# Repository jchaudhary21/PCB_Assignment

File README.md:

# PCB Design Based on F4BY board

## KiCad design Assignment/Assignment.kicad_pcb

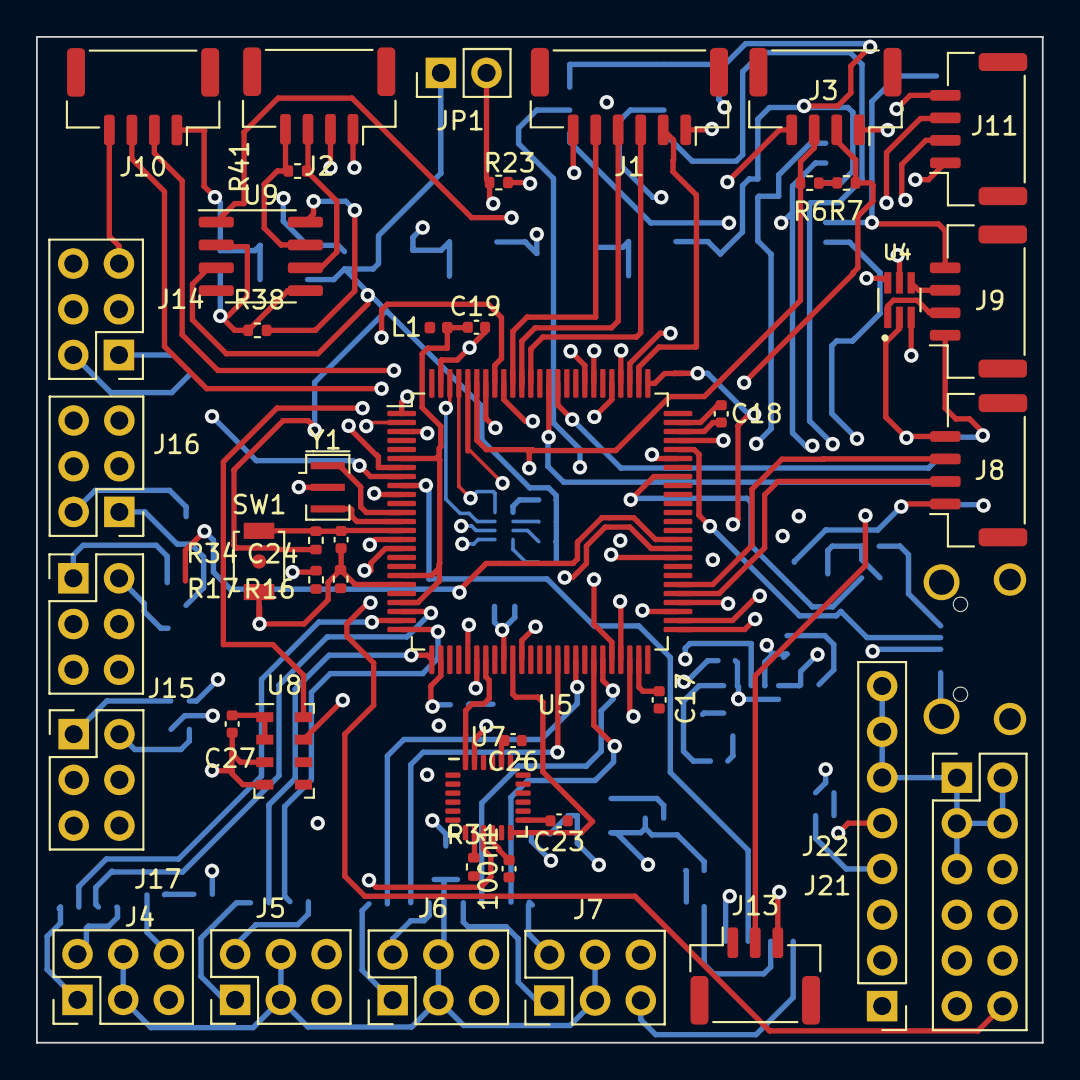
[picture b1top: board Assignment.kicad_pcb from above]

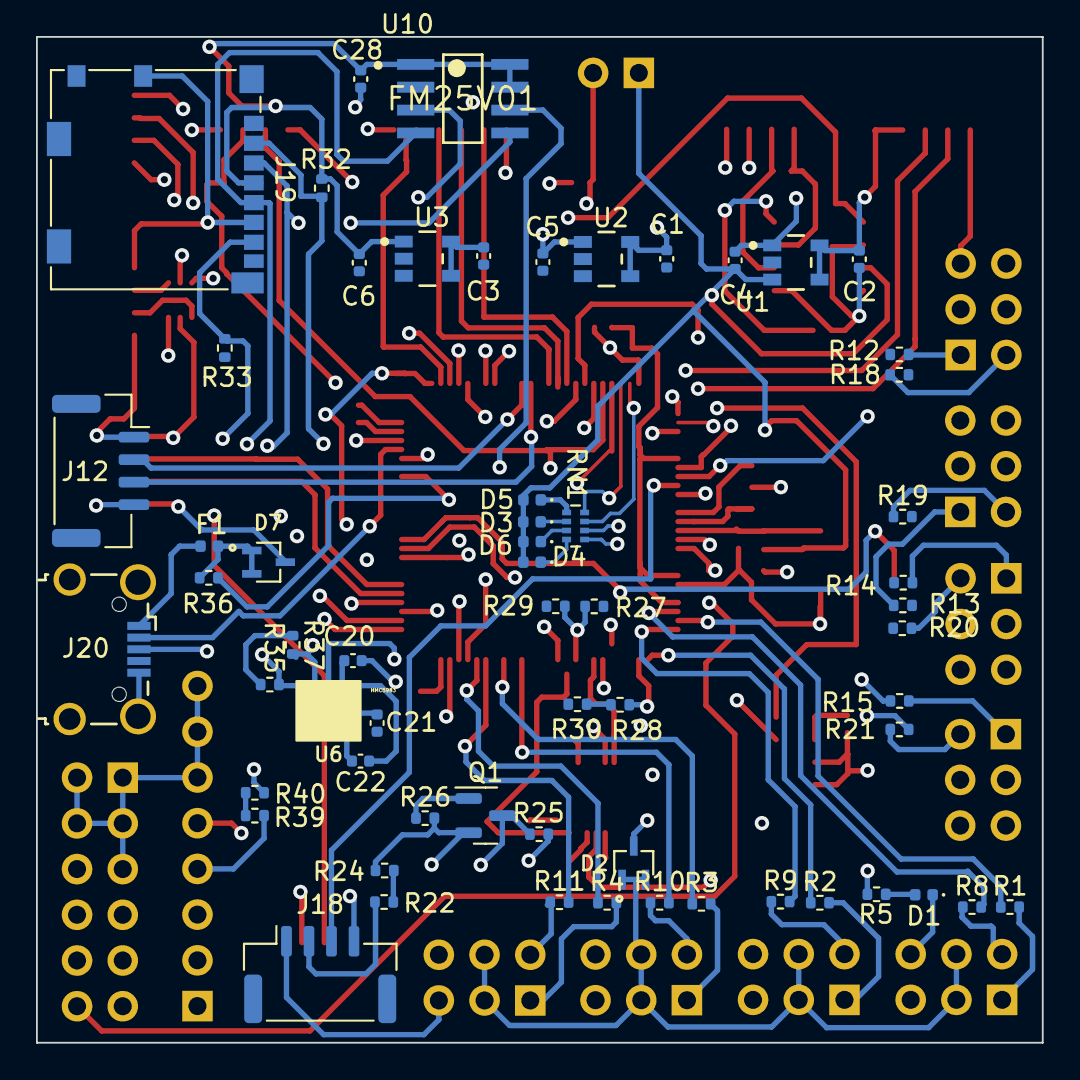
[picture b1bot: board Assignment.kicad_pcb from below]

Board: 4 copper layers, 55.9 x 55.9 mm, 105 parts (61 on the bottom side), 116 nets.

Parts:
100n1: C; C_0402_1005Metric
C1, C2, C3: 1uF; C_0402_1005Metric
C4, C5, C6: 2.2uF; C_0402_1005Metric
C17, C18, C20, C21, C22, C27: C; C_0402_1005Metric
C19, C24: C_Small; C_0402_1005Metric
C23, C26, C28: 100n; C_0402_1005Metric
D1, D3, D4, D5, D6: LED; LED_0402_1005Metric
D2, D7: Dual_Diode; SOT65P205X100-3N
F1: 500mA; Fuse_0402_1005Metric
J1: Conn_01x06_Male; JST_GH_SM06B-GHS-TB_1x06-1MP_P1.25mm_Horizontal
J2, J3, J8, J9, J10, J11, J12, J18: Conn_01x04_Male; JST_GH_SM04B-GHS-TB_1x04-1MP_P1.25mm_Horizontal
J4, J5, J6, J7, J14, J15, J16, J17: Conn_02x03_Odd_Even; PinHeader_2x03_P2.54mm_Vertical
J13: Conn_01x03_Male; JST_GH_SM03B-GHS-TB_1x03-1MP_P1.25mm_Horizontal
J19: Micro_SD_Card; microSD_HC_Molex_104031-0811
J20: USB_B_Micro; USB_Micro-B_Wuerth_629105150521_CircularHoles
J21: Conn_02x06_Counter_Clockwise; PinHeader_2x06_P2.54mm_Vertical
J22: Conn_01x08_Male; PinHeader_1x08_P2.54mm_Vertical
JP1: Solder Jumper; PinHeader_1x02_P2.54mm_Vertical
L1: INDUCTOR (L_1); L_0402_1005Metric
Q1: BSS123; SOT-23
R1, R2, R3, R4, R8, R9, R10, R11, R12, R13, R14, R15, R18, R19, R20, R21: 100E; R_0402_1005Metric
R5: 560E; R_0402_1005Metric
R6, R7, R22, R32, R33, R34, R35, R36, R37: R; R_0402_1005Metric
R16, R17, R38, R39, R40, R41: 10k; R_0402_1005Metric
R23, R25, R27, R28, R29, R30, R31: 10K; R_0402_1005Metric
R24: 15K; R_0402_1005Metric
R26: 1K; R_0402_1005Metric
RN1: 330E; R_Array_Concave_4x0402
SW1: SW_MEC_5G; SW_SPST_B3U-1000P-B
U1, U2, U3: MIC5233-33; Microchip-SOT23-5LD-PL-1-0-0-MFG
U4: 74LVC2GU04; SOT65P210X110-6N
U5: STM32F407VGTx; LQFP-100_14x14mm_P0.5mm
U6: HMC5983; HMC5983-TR
U7: MPU-6000; InvenSense_QFN-24_4x4mm_P0.5mm
U8: MS5611-01BA; LGA-8_3x5mm_P1.25mm
U9: MAX3051; SOIC-8_3.9x4.9mm_P1.27mm
U10: FM25V01; Cypress_Semiconductor-51-85066-0-H-IPC_A
Y1: Resonator; Resonator_SMD_Murata_CSTxExxV-3Pin_3.0x1.1mm

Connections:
+5V: C1.1, C2.1, C3.1, D2.3 (K), D7.3 (K), J1.1, J2.2, J3.1, J8.1, J9.1, J10.1, J11.1, J12.1, J14.3, J14.4, J15.3, J15.4, J16.3, J16.4, J17.3, J17.4, J18.4, J21.7, J22.1, J22.2, J22.3, R5.1, R25.1, R30.1, U1.4, U1.5, U2.4, U2.5, U3.4, U3.5
BOOT: JP1.2 (B), R23.2, U5.94 (BOOT0)
BUZZER: J21.6, Q1.3 (D), R25.2
CAN1_RX: U5.81 (PD0), U9.4 (RXD)
CAN1_TX: U5.82 (PD1), U9.1 (TXD)
CANH: J2.4, R41.1, U9.7 (CANH)
CANL: J2.3, R41.2, U9.6 (CANL)
CBYD: U1.2, U2.2, U3.2
CS_SD: J19.2 (DAT3/CD), R32.2, U5.46 (PE15)
CURR: R39.1, R40.1, U5.17 (PC2)
ECHO: R22.2, R24.2, U5.5 (PE6)
G1: J21.8, U5.3 (PE4)
G2: J21.9, U5.7 (PC13)
G3: J21.10, U5.8 (PC14)
GND: 100n1.1, C1.2, C2.2, C3.2, C4.2, C5.2, C6.2, C17.1, C18.1, C19.2, C20.2, C21.2, C23.1, C24.2, C26.1, C27.2, C28.2, D1.1 (K), J1.6, J2.1, J3.4, J4.5, J4.6, J5.5, J5.6, J6.5, J6.6, J7.5, J7.6, J8.4, J9.4, J10.4, J11.4, J12.4, J14.5, J14.6, J15.5, J15.6, J16.5, J16.6, J17.5, J17.6, J18.1, J19.6 (VSS), J19.9 (SHIELD), J20.5 (GND), J20.6 (Shield), Q1.2 (S), R16.1, R23.1, R24.1, R26.2, R27.1, R28.1, R38.2, R40.2, SW1.1 (A), U1.1, U2.3, U3.3, U4.2 (GND), U5.10 (VSS), U5.20 (VSSA), U5.27 (VSS), U5.37 (PB2), U5.74 (VSS), U5.99 (VSS), U7.1 (CLKIN), U7.11 (FSYNC), U7.18 (GND), U8.3 (GND), U8.4 (CSB), U8.5 (CSB), U9.2 (GND), U9.5 (SHDN), Y1.2
GPS_RX: J8.3, U5.56 (PD9)
GPS_TX: J8.2, U5.55 (PD8)
I2C1_SCL: J3.3, R6.2, U5.95 (PB8), U8.8 (SCLK)
I2C1_SDA: J3.2, R7.2, U5.96 (PB9), U8.7 (SDI/SDA)
INT_MAG: U5.36 (PB1), U6.DRDY
INT_MPU: U5.35 (PB0), U7.12 (INT)
IN_T4_1: R15.1, U5.59 (PD12)
IN_T4_2: R21.2, U5.60 (PD13)
IN_T4_3: R14.1, U5.61 (PD14)
IN_T4_4: R20.2, U5.62 (PD15)
MOTOR_1: R8.2, U5.23 (PA0)
MOTOR_2: R1.1, U5.24 (PA1)
MOTOR_3: R9.2, U5.25 (PA2)
MOTOR_4: R2.1, U5.26 (PA3)
MOTOR_5: R10.2, U5.40 (PE9)
MOTOR_6: R3.1, U5.42 (PE11)
MOTOR_7: R11.2, U5.44 (PE13)
MOTOR_8: R4.1, U5.45 (PE14)
NRST: C24.1, R34.2, SW1.2 (A), U5.14 (NRST)
unnamed: 100n1.2, U7.10 (REGOUT)
unnamed: C17.2, U5.49 (VCAP_1)
unnamed: C18.2, U5.73 (VCAP_2)
unnamed: C19.1, L1.2, U5.6 (VBAT), U5.19 (VDD), U5.22 (VDDA)
unnamed: C21.1, U6.C1
unnamed: C22.1, U6.SETC
unnamed: C22.2, U6.SETP
unnamed: C26.2, U7.20 (CPOUT)
unnamed: D1.2 (A), R5.2
unnamed: D3.1 (K), RN1.6 (R3.2)
unnamed: D4.1 (K), RN1.8 (R1.2)
unnamed: D5.1 (K), RN1.5 (R4.2)
unnamed: D6.1 (K), RN1.7 (R2.2)
unnamed: D7.1 (A), D7.2 (A), F1.1, R36.1
unnamed: F1.2, J20.1 (VBUS)
unnamed: J4.1, R1.2
unnamed: J4.2, R8.1
unnamed: J5.1, R2.2
unnamed: J5.2, R9.1
unnamed: J6.1, R3.2
unnamed: J6.2, R10.1
unnamed: J7.1, R4.2
unnamed: J7.2, R11.1
unnamed: J9.2, U4.1
unnamed: J9.3, U4.4
unnamed: J14.1, R12.2
unnamed: J14.2, R18.1
unnamed: J15.1, R13.2
unnamed: J15.2, R19.1
unnamed: J16.1, R14.2
unnamed: J16.2, R20.1
unnamed: J17.1, R15.2
unnamed: J17.2, R21.1
unnamed: J18.2, R22.1
unnamed: J21.1, J21.2, J21.3, J21.4, J21.5, J22.6, J22.7, J22.8
unnamed: J22.4, R39.2
unnamed: R16.2, R17.2, U5.18 (PC3)
unnamed: R38.1, U9.8 (RS)
unnamed: U5.12 (PH0), Y1.1
unnamed: U5.13 (PH1), Y1.3
PA4: R31.2, U5.29 (PA4), U7.8 (~CS)
PA5: U5.30 (PA5), U7.23 (SCL/SCLK)
PA6: U5.31 (PA6), U7.9 (AD0/MISO)
PA7: U5.32 (PA7), U7.24 (SDA/MOSI)
PA9: R36.2, U5.68 (PA9)
PA11: J20.3 (D+), U5.70 (PA11)
PA12: J20.2 (D-), U5.71 (PA12)
PB10: R35.2, U5.47 (PB10), U6.SCL/SPI_SCK
PB11: R37.2, U5.48 (PB11), U6.SDA/SPI_SDI
PE0: RN1.4 (R4.1), U5.97 (PE0)
PE1: RN1.3 (R3.1), U5.98 (PE1)
PE2: RN1.2 (R2.1), U5.1 (PE2)
PE3: RN1.1 (R1.1), U5.2 (PE3)
PE5: Q1.1 (G), R26.1, U5.4 (PE5)
POWER_SENCE: R28.2, R30.2, U5.33 (PC4)
POWER_SERVO_SENCE: R27.2, R29.2, U5.34 (PC5)
P_RX: J10.3, U5.93 (PB7)
P_TX: J10.2, U5.92 (PB6)
RSSI: J21.12, U5.16 (PC1)
SERVO_POWER: D2.1 (A), D2.2 (A), J4.3, J4.4, J5.3, J5.4, J6.3, J6.4, J7.3, J7.4, R29.1
SPEED: J21.11, U5.15 (PC0)
SPI2_CS: U5.51 (PB12), U10.3
SPI2_MISO: J19.7 (DAT0), R33.1, U5.53 (PB14), U10.6
SPI2_MOSI: J19.3 (CMD), U5.54 (PB15), U10.5
SPI2_SCK: J19.5 (CLK), U5.52 (PB13), U10.4
SPI3_CS: J1.2, U5.77 (PA15)
SPI3_MISO: J1.4, U5.90 (PB4)
SPI3_MOSI: J1.5, U5.91 (PB5)
SPI3_SCK: J1.3, U5.89 (PB3)
SWCLK: J13.3, U5.76 (PA14)
SWDIO: J13.2, U5.72 (PA13)
TEL_RX: J12.3, U5.87 (PD6)
TEL_TX: J12.2, U5.86 (PD5)
TRIGGER: J18.3, U5.9 (PC15)
USART4_RX: U4.6, U5.79 (PC11)
USART4_TX: U4.3, U5.78 (PC10)
USART5_RX: J11.3, U5.83 (PD2)
USART5_TX: J11.2, U5.80 (PC12)
VCC_1: C4.1, C27.1, D3.2 (A), D4.2 (A), D5.2 (A), D6.2 (A), JP1.1 (A), L1.1, R6.1, R7.1, R34.1, R35.1, R37.1, U1.3, U4.5 (VCC), U5.11 (VDD), U5.28 (VDD), U5.50 (VDD), U5.75 (VDD), U5.100 (VDD), U8.1 (VDD), U8.2 (PS), U9.3 (VDD)
VCC_2: C5.1, C20.1, C23.2, R31.1, U2.1, U6.VDD, U6.VDDIO, U7.13 (VDD)
VCC_3: C6.1, C28.1, J19.4 (VDD), R32.1, R33.2, U3.1, U10.1, U10.7, U10.8
V_IN: J22.5, R17.1

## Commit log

2023-05-21 added schematic files
2023-05-24 Clean up
2023-05-26 Create Assignment
    Added Assignment Folder
2023-05-26 added Assignment file
2023-05-26 change folder position
2023-05-26 remane folder name
2023-06-07 added PCB Layout
2023-06-07 remove unwanted files
2023-06-07 added files
